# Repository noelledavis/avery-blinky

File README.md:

# avery-blinky

Blinky LED triangles for Avery House

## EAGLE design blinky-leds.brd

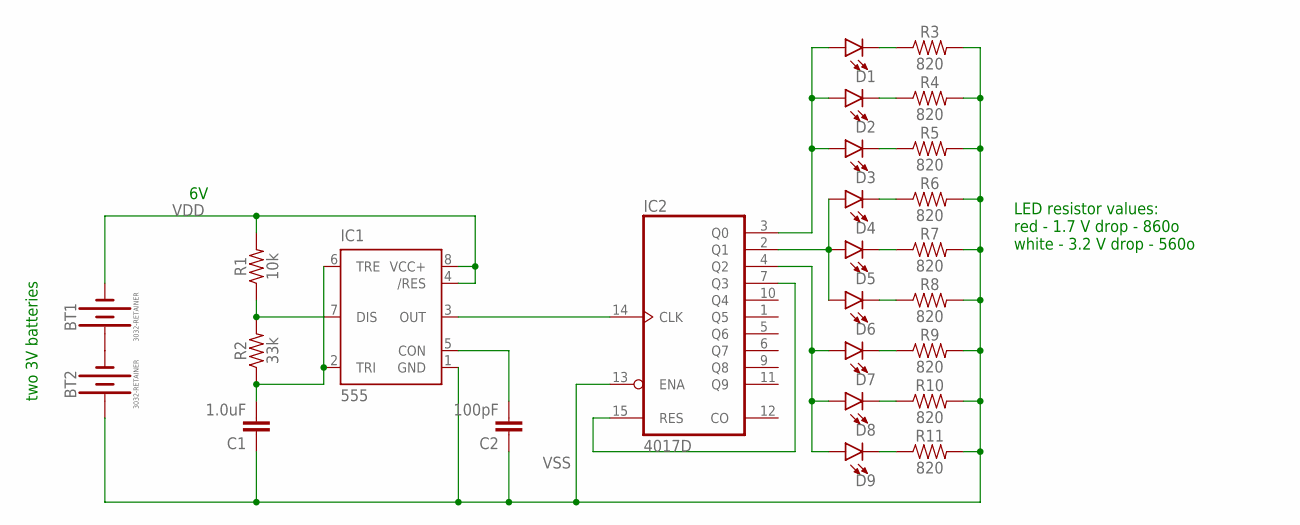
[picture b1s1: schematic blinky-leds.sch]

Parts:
BT1, BT2: 3032-RETAINER; KEYSTONE-3034
C1: 1.0uF; 0603
C2: 100pF; 0603
D1, D2, D3, D4, D5, D6, D7, D8, D9: LED0603; LED-0603
IC1: 555; SO08
IC2: 4017D; SO16
R1: 10k; 0603
R2: 33k; 0603
R3, R4, R5, R6, R7, R8, R9, R10, R11: 820; 0603

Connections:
unnamed: BT1.P$1 (+), BT2.P$2 (-), BT2.P$3 (-)
unnamed: D6.C, R8.1
unnamed: D1.A, D2.A, D3.A, IC2.3 (Q0)
unnamed: D4.A, D5.A, D6.A, IC2.2 (Q1)
unnamed: IC1.3 (OUT), IC2.14 (CLK)
unnamed: C2.2, IC1.5 (CON)
unnamed: IC1.7 (DIS), R1.1, R2.2
unnamed: C1.2, IC1.2 (TRI), IC1.6 (TRE), R2.1
unnamed: IC2.7 (Q3), IC2.15 (RES)
unnamed: D5.C, R7.1
unnamed: D4.C, R6.1
unnamed: D3.C, R5.1
unnamed: D2.C, R4.1
unnamed: D1.C, R3.1
unnamed: D9.C, R11.1
unnamed: D8.C, R10.1
unnamed: D7.C, R9.1
unnamed: D7.A, D8.A, D9.A, IC2.4 (Q2)
VDD: BT1.P$2 (-), BT1.P$3 (-), IC1.4 (/RES), IC1.8 (VCC+), IC2.16 (VDD), R1.2
VSS: BT2.P$1 (+), C1.1, C2.1, IC1.1 (GND), IC2.8 (VSS), IC2.13 (ENA), R3.2, R4.2, R5.2, R6.2, R7.2, R8.2, R9.2, R10.2, R11.2

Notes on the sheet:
LED resistor values: red - 1.7 V drop - 860o white - 3.2 V drop - 560o
two 3V batteries

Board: 2 copper layers, 26 parts (0 on the bottom side), 20 nets, no tracks yet.

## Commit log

2019-09-26 Made schematic
2019-09-26 Added gitignore, README
2019-09-26 Added missing LEDs, updated library
2019-09-27 Right schematic

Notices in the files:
parts and their libraries:
SparkFun-Capacitors: Licensing: Creative Commons ShareAlike 4.0 International - https://creativecommons.org/licenses/by-sa/4.0
